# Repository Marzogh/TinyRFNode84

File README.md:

# TinyRFNode84
Wireless Sensor node based on Attiny84 and RFM69W

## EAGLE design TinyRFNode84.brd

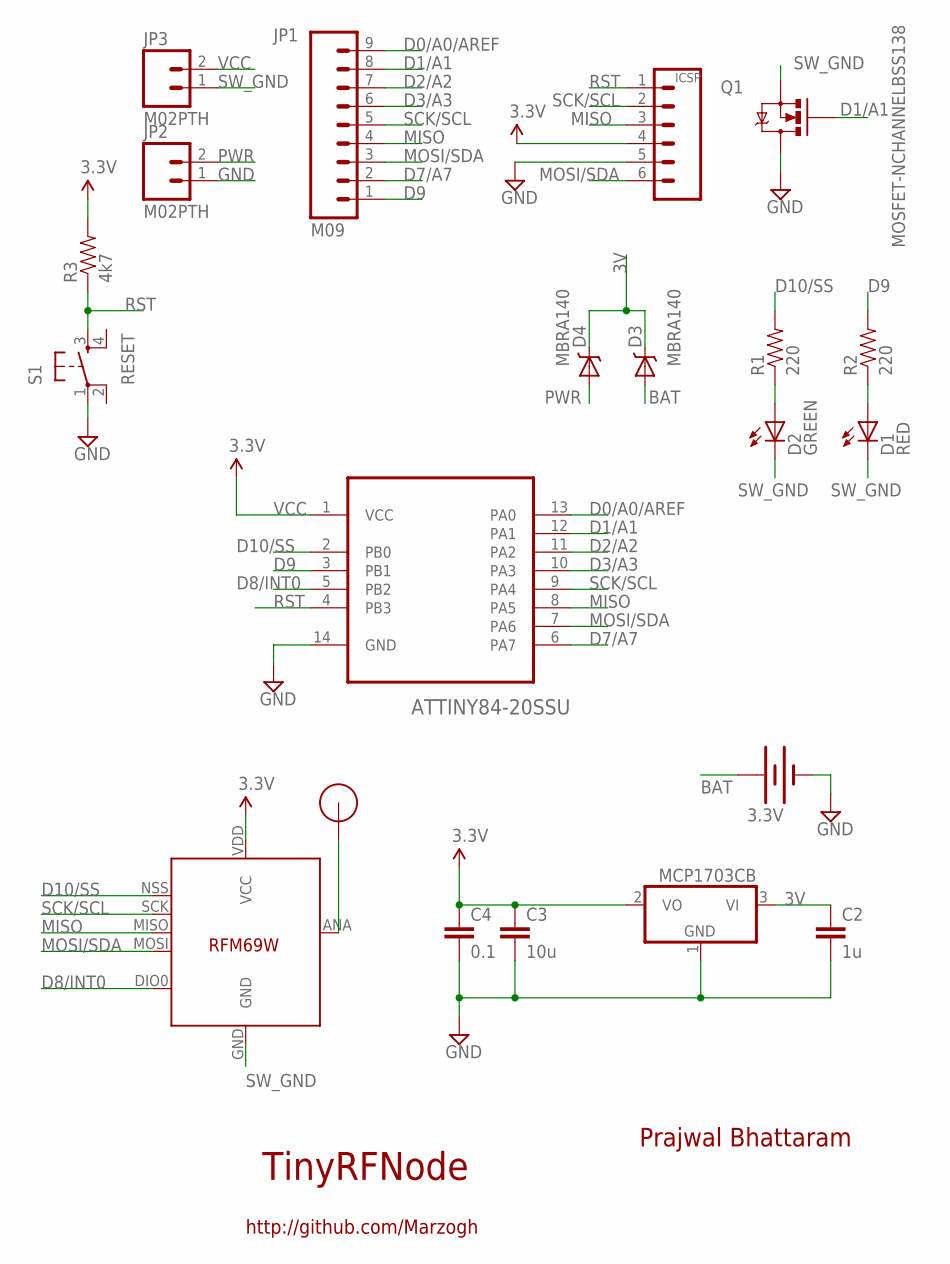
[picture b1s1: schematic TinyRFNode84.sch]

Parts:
BAT1: 3.3V; BATTCON_12MM
C2: 1u; 0603-CAP
C3: 10u; 0805-CAP
C4: 0.1; 0603-CAP
D1: RED; LED-0603
D2: GREEN; LED-0603
D3, D4: MBRA140; SMA-DIODE
IC3: MCP1703CB; SOT23
ICSP: ICSP; 1X06_NO_SILK
JP1: M09; 1X09
JP2, JP3: M02PTH; 1X02
Q1: MOSFET-NCHANNELBSS138; SOT23
R1, R2: 220; 0603-RES
R3: 4k7; 0402-RES
S1: RESET; TACTILE-SWITCH-SMD
U1: ATTINY84-20SSU; SOIC127P600X175-14N
U$1: RFM12B_ANTENNA; RFM12B-ANTENNA
U$5: RFM69; RFM69W-MINPADS

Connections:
3V: C2.1, D3.C, D4.C, IC3.3 (VI)
BAT: BAT1.PWR@1 (+), D3.A
D0/A0/AREF: JP1.9, U1.13 (PA0)
D1/A1: JP1.8, Q1.1 (G), U1.12 (PA1)
D2/A2: JP1.7, U1.11 (PA2)
D3/A3: JP1.6, U1.10 (PA3)
D7/A7: JP1.2, U1.6 (PA7)
D8/INT0: U1.5 (PB2), U$5.DIO0
D9: JP1.1, R2.2, U1.3 (PB1)
D10/SS: R1.2, U1.2 (PB0), U$5.NSS (SEL)
GND: BAT1.GND (-), C2.2, C3.2, C4.2, IC3.1 (GND), ICSP.5, JP2.1, Q1.3 (D), S1.1, U1.14 (GND)
MISO: ICSP.3, JP1.4, U1.8 (PA5), U$5.MISO
MOSI/SDA: ICSP.6, JP1.3, U1.7 (PA6), U$5.MOSI
unnamed: U$1.P$1, U$5.ANA (ANT)
unnamed: D1.A, R2.1
unnamed: D2.A, R1.1
PWR: D4.A, JP2.2
RST: ICSP.1, R3.1, S1.3, U1.4 (PB3)
SCK/SCL: ICSP.2, JP1.5, U1.9 (PA4), U$5.SCK
SW_GND: D1.C, D2.C, JP3.1, Q1.2 (S), U$5.GND
VCC: C3.1, C4.1, IC3.2 (VO), ICSP.4, JP3.2, R3.2, U1.1 (VCC), U$5.VDD (VCC)

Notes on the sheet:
TinyRFNode
Prajwal Bhattaram
http://github.com/Marzogh

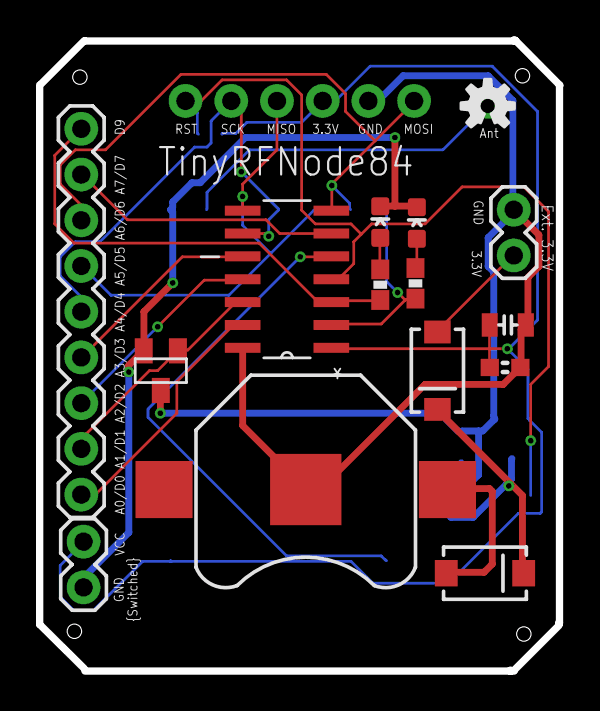
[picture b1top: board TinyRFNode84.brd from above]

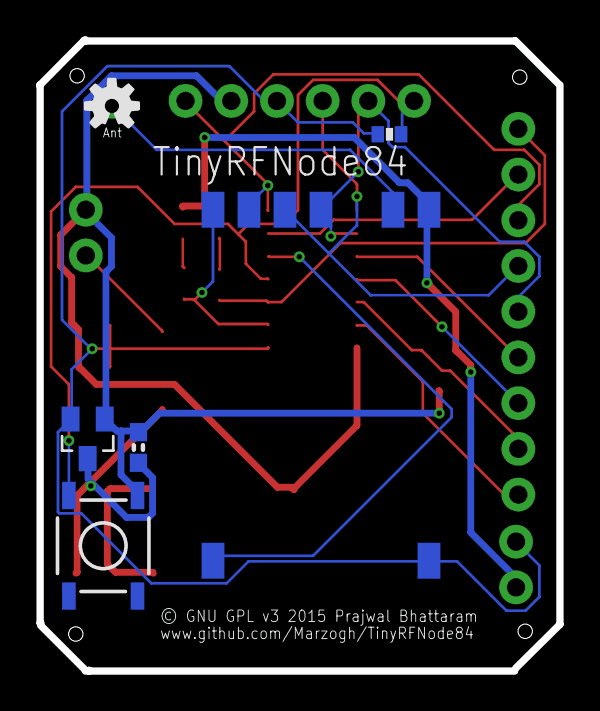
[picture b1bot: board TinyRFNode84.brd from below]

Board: 2 copper layers, 28.9 x 35.1 mm, 23 parts (6 on the bottom side), 21 nets.

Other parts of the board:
U$2, U$3: OSHW-LOGO-S

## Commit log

2015-05-07 Added schematics, board design and gerbers
2015-05-07 Added board and schematic images
2015-05-07 Fixed a few routing errors
2015-08-07 Name change
2015-08-07 v2.0.2
2015-08-07 added .gitignore
2015-08-07 deletion

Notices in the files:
TinyRFNode84.brd:
© GNU GPL v3 2015 Prajwal Bhattaram
parts and their libraries:
SparkFun-Connectors: Licensing: Creative Commons ShareAlike 4.0 International - https://creativecommons.org/licenses/by-sa/4.0
